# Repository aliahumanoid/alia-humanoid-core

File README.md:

<p align="center">
  <picture>
    <source media="(prefers-color-scheme: dark)" srcset="docs/media/alia-banner-dark.png">
    
  </picture>
</p>

# Alia Humanoid

**Building humanoid mechanics inside real human proportions.**

<table>
<tr>
<td width="70%">

</td>
<td width="30%">

</td>
</tr>
<tr>
<td align="center"><i>Lower leg assembly — human scale comparison</i></td>
<td align="center"><i>Right ankle prototype — 2-DOF motion test</i></td>
</tr>
</table>

<table>
<tr>
<td width="65%">
  
</td>
<td width="35%">
  
</td>
</tr>
<tr>
<td align="center"><i>Knee joint overlay — Joint Design Log #002</i></td>
<td align="center"><i>Right knee prototype — 1-DOF motion test</i></td>
</tr>
</table>

<table>
<tr>
<td align="center">

</td>
</tr>
<tr>
<td align="center"><i>First natural walking gait — physics simulation, motion-tracking RL (June 2026). Not hardware yet: sim-to-real is gated by remaining hardware.</i></td>
</tr>
</table>

---

## What We're Building

A humanoid robot designed from the ground up to fit within real human dimensions and proportions. 

Most humanoid projects scale UP for easier engineering — more space for motors, looser tolerances, simpler thermal management. We do the opposite: **building inside human constraints** forces design decisions — motor placement, transmission routing, thermal budget — that larger-envelope projects can avoid.

The result? A robot that can fit human environments, wear human clothing, and interact at human scale — using tendon-driven actuation, custom motor placement, and tight mechanical integration.

**Current Phase 0 Focus:** Lower body (hip + knee + ankle) — tendon-driven and direct-drive actuation.

### How We Develop in the Open

This repository carries the **replication core** — firmware, protocols, base host operation, hardware documentation, and results. Advanced lab tooling (calibration campaigns, learning-control experiments, gait tooling) is developed in a private suite and opens progressively as milestones mature. Results, videos, logs, and writeups continue to be published openly. We publish what fails alongside what works; simulation results are labeled as simulation results.

### Latest Updates
- 2026-11-09: Joint Design Log #003 (Hip) published — [YouTube](https://youtu.be/a9sh70xy4z0)
- 2026-09: **Hip roll motor integrated — first 3-DOF runs on the bench.** The two tendon-driven DOFs and the direct-drive roll now run together on one joint controller; results with the next Joint Design Log
- 2026-08-27: **Hip on the bench — first run at natural walking speed.** The 2-DOF tendon-driven hip tracks a gait-like reference (flexion and abduction sines in quadrature, 1.1 s cycle), free swing with no external load, with one learned feed-forward correction from a previous run (uncorrected at the same speed: 6.0° / 2.0° rms): 27 cycles, 2.95° / 1.37° rms, repeatable run to run — [X post](https://x.com/AliaHumanoid/status/2092992852150108425) (the post calls it the simulation policy's walking trajectory; the reference was a synthetic gait-like cycle)
- 2026-08: Direct-drive hip roll validated on a separate single-motor bench, free shaft (reference persistence, sweeps; a ±6° segment of the simulated walking trajectory tracked on hardware at 0.28° rms with the motor-internal loop, best run after timing and learning-control correction)
- 2026-07: **Development drop** — control-loop rate hardening (bench-validated to 625 Hz on the ankle), joint-map capture improvements, saved-offset warm-boot fast path, MOTION GUARD V2 (gait-aware safety guards; ships disabled, bench validation pending), host impedance-stream `tau_ff` channel — [details](PUBLIC_UPDATES.md)
- 2026-07-18: **Technical note published:** [Deterministic boot-time offset reconstruction for tendon-driven joints](https://aliahumanoid.com/notes/deterministic-boot-offset-reconstruction.html) — method published as prior art
- 2026-07: **License change:** software is GPLv3 from this release (prior MIT snapshots remain MIT); protocol specs stay MIT; hardware licensing unchanged — [rationale](PUBLIC_UPDATES.md)
- 2026-06-04: **First natural walking gait in simulation** — motion-tracking RL on the lower body, ONNX-verified locally — [X thread](https://x.com/AliaHumanoid/status/2062545958991265831) · [details](PUBLIC_UPDATES.md)
- 2026-06: Per-joint power board (`rev_d_power`) bench-validated end-to-end — closed-loop motor control on real hardware, 0.08° tracking error ([report](hardware/electronics/joint_controller_board/rev_d_power/BENCH_VALIDATION_REPORT.md) · [known issues](hardware/electronics/joint_controller_board/rev_d_power/README.md))
- 2026-04: Hip hybrid firmware path implemented (3 DOF / 5 motors)
- 2026-01-26: Joint Design Log #002 (Knee) published — [YouTube](https://youtu.be/4jU5Na2z-s8) · [X thread](https://x.com/AliaHumanoid/status/2015812906101657848)
- 2025-11-13: Joint Design Log #001 (Ankle) published — [YouTube](https://youtu.be/1Z9GlTnYEFs)
- 2025-10-31: Phase 0 public release — [PUBLIC_UPDATES.md](PUBLIC_UPDATES.md)

### Key Features

- 🦶 **2-DOF Ankle Joint**
  Plantarflexion/dorsiflexion (-50° to +25°) + inversion/eversion (±25°)

- 🦵 **1-DOF Knee Joint**
  Full flexion/extension (0° to 100°) with antagonistic tendon pair

- 🦴 **3-DOF Hip Joint (Hybrid)**
  Flexion/extension + abduction/adduction (tendon-driven) + axial roll (direct-drive), 5 motors

- 🧵 **Tendon-Driven Actuation**
  Antagonistic motor pairs with cascade PID, plus single direct-drive for hip roll

- 📏 **Human-Scaled Design**  
  Designed inside real human leg envelope — not scaled up

- ⚙️ **Real Hardware Iteration**  
  PA12 nylon structure (multi jet fusion), pin-and-bushing joints, UHMWPE tendons

- 🖥️ **Jetson Multi-Joint Controller**
  CAN-direct impedance streaming at 50Hz, automated exercise patterns, CAN-first diagnostics

- 🚶 **Walking — In Simulation**
  Natural full-amplitude gait via motion-tracking RL (knee ROM ~57°, foot clearance ~14 cm); sim-to-real gated by remaining hardware

- 📂 **Files released in phases**
  Phased licensing roadmap: STL → STEP → CAD source

---

## What Works ✅ / What Doesn't ⚠️

We document **both successes and failures** transparently.

> **Safety:** before powering any joint, read [Known safety limitations](SAFETY_LIMITATIONS.md).

**Current validation snapshot: knee and ankle closed as architecture baselines; per-joint power board bench-validated (known issues documented); hip tendon DOFs validated on the bench and the direct-drive roll on a single-motor bench, first 3-DOF runs on the bench; natural walking gait achieved in simulation, gait-like trajectory tracked on the physical hip at natural walking speed**

### ✅ Validated On Hardware (Phase 0)

- Knee validated as single-controller baseline (`L1` closed) — [Joint Design Log #002](https://youtu.be/4jU5Na2z-s8)
- Ankle validated as single-controller baseline (`L2` closed) — [Joint Design Log #001](https://youtu.be/1Z9GlTnYEFs)
- Multi-joint Jetson coordination operational on bench (`KNEE_RIGHT + ANKLE_RIGHT`) — [milestone log](PUBLIC_UPDATES.md)
- Protocol v1.0 freeze documented for the current knee+ankle bench baseline — [CAN system architecture §4.5](software/docs/CAN_SYSTEM_ARCHITECTURE.md)
- Ankle kinematics achieve target ROM (2 DOF within human envelope) — [joint specs](docs/specs/README.md)
- Knee ROM and tendon-driven position control validated (0-100 degrees)
- UHMWPE tendons validated for current bench loads and pulley compatibility — [tendon specs](docs/specs/TENDON_SPECIFICATIONS.md)
- PA12 structure passes current static/load validation
- Peak torque within biomechanics requirements at the validated bench conditions — [motor specs](docs/specs/MOTOR_SPECIFICATIONS.md)
- Rolling impedance control via CAN with cascade PID on the validated tendon-driven joints — [operational guide](software/docs/SET_IMPEDANCE_OPERATIONAL_GUIDE.md)
- Per-joint power board (`rev_d_power`) validated end-to-end: power rails, hot-swap protection, health telemetry, closed-loop motor control (0.08° tracking error) — [bench report](hardware/electronics/joint_controller_board/rev_d_power/BENCH_VALIDATION_REPORT.md) · [known issues](hardware/electronics/joint_controller_board/rev_d_power/README.md) (motor rail sags on touch or gate-node contamination; handling rules)

### 🧪 Validated In Simulation (Not Hardware)

- Natural full-amplitude walking gait via motion-tracking RL (knee ROM ~57°, foot clearance ~14 cm)
- Policy exported to ONNX and verified locally with observation-parity checks
- Robustness via domain randomization (actuator gains, latency, mass) grounded in measured bench data
- **Honest boundary:** simulation results are simulation results — hardware walking requires foot sole, batteries and full-leg integration first

### ✅ Hip — Per-Axis Bench Validation (August–September 2026)

Bench runs used firmware changes that ship with the next release, and host-side gait-replay tooling (timing and learned corrections) that stays in the private suite; this release carries the hybrid model and the `HIP_ROLL_BENCH_*` profiles.

- Hip hybrid model (`3 DOF / 5 motors`, per-DOF `DriveType` / `DofCapabilityFlags`) exercised on hardware: both tendon-driven DOFs mapped, calibrated and driven with the hybrid-aware auto-mapping path (known issue: at the end of a mapping run all motors are released and, with the tendons slack, a gravity-loaded limb drops freely; support the limb before the run ends; a slow slack take-up is in development)
- Joint encoders zeroed at the CAD mechanical stops, persistent across power cycles
- Gait-like reference (flexion and abduction sines in quadrature, 1.1 s cycle) tracked on the physical hip (2 tendon-driven DOFs) at natural walking speed, free swing with no external load, with one learned feed-forward correction from a previous run (uncorrected at the same speed: 6.0° / 2.0° rms): 27 cycles, 2.95° / 1.37° rms, repeatable run to run — [X post](https://x.com/AliaHumanoid/status/2092992852150108425) (the post calls it the simulation policy's walking trajectory; the reference was a synthetic gait-like cycle)
- Direct-drive axial roll validated on a separate single-motor bench, free shaft (`HIP_ROLL_BENCH_*` profiles): reference persistence across power cycles, sweeps, a ±6° segment of the simulated walking trajectory tracked on hardware at 0.28° rms with the motor-internal loop (best run, after timing and learning-control correction)

### 🛠️ Implemented In Firmware, Pending Bench Validation

- MOTION GUARD V2 — gait-aware divergence/stall guards behind a runtime mode switch (ships in LEGACY mode = current behavior; SHADOW/ACTIVE pending bench validation)

### ⚠️ Still Iterating

- Hip: roll motor mounted, the two tendon-driven DOFs and the roll run together on one controller (September 2026); 3-DOF tracking on the bench in progress, results with the next Joint Design Log, then mounting into the full right leg
- Full hip 3-DOF integrated validation (L3)
- Multi-controller integrated test (L5: hip + knee + ankle on Jetson)
- Walking gait as integrated lower-body system **on hardware**
- Sim-to-real transfer (policy deployment on the onboard computer; gated by foot sole, power boards at scale, batteries)
- Power board high-current stress testing (22A continuous / ~38A peak)

---

## Architecture

```
Jetson host (Python)          RP2350 joint controller (C++)          Motors
SET_IMPEDANCE @50Hz  --CAN-->  core0: encoders (MT6835, SPI)   --CAN--> antagonistic
per-DOF gains/tau_ff           core1: cascade PID + safety              tendon pairs
                               (bench-validated to 625 Hz)              (+ direct-drive hip roll)
```

- [CAN system architecture](software/docs/CAN_SYSTEM_ARCHITECTURE.md) — protocol, IDs, freeze policy
- [SET_IMPEDANCE operational guide](software/docs/SET_IMPEDANCE_OPERATIONAL_GUIDE.md) — the impedance streaming interface
- [Firmware update protocol spec](software/docs/CAN_FIRMWARE_UPDATE_PROTOCOL_SPEC.md) — CAN-based firmware updates

## Build & Run

**Host (runs without hardware):**
```bash
cd software/host && python3 -m venv venv && . venv/bin/activate
pip install -r requirements.txt && python main.py   # web UI on :5001
```

**Firmware (PlatformIO, RP2350 Pico 2):**
```bash
cd software/firmware/joint_controller && pio run
```

Bench bring-up: [Jetson single-controller checklist](software/docs/JETSON_SINGLE_CONTROLLER_BRINGUP_CHECKLIST.md). Minimum bench: one joint controller board, CAN adapter, 24V supply.

## Current Status (Phase 0)

Last reviewed: 2026-11-09. Ankle and knee validated as single-controller baselines; hip on the bench; walking shown in simulation only.

| Component | Status | License | Notes |
|-----------|--------|---------|-------|
| **Software** | ✅ Public | GPLv3 | Python host + C++ firmware (RP2350 Pico 2); releases before July 2026 remain MIT |
| **Hardware Docs** | ✅ Public | CC BY-NC-ND | Assembly guides, BOM, design specs |
| **STL Files** | ✅ Public | CC BY-NC-ND | 19 files: ankle, lower leg, common components |
| **Electronics** | ✅ Public | CC BY-NC-ND | RP2350 controller board + per-joint power board (KiCad source, Gerber, STEP) |
| **CAD Source** | 📅 Phase 2+ (TBD) | CC BY-SA | Full parametric Fusion 360 timeline |

See our [licensing roadmap](hardware/LICENSE.md) for details on what is released when.

---

## Quick Links

- 📺 **[YouTube Channel](https://www.youtube.com/@aliahumanoid)** — Design logs, demos, technical breakdowns
- 🐦 **[X/Twitter (@AliaHumanoid)](https://x.com/AliaHumanoid)** — Project updates, iteration logs
- 🌐 **[Website](https://aliahumanoid.com)** — Project overview and roadmap
- 📝 **[Public Updates](PUBLIC_UPDATES.md)** — Public milestone log and release notes
- 📖 **[Documentation](software/README.md)** — Software architecture, protocols, build guides
- 📐 **[Technical Specs](docs/specs/README.md)** — Joint specifications, motor specs, tendon specs
- 🗒️ **[Technical Notes](https://aliahumanoid.com/notes/deterministic-boot-offset-reconstruction.html)** — Method writeups published as prior art

**Evaluating this project? Start here:** (1) watch a [joint design log](https://youtu.be/1Z9GlTnYEFs), (2) read the [boot-reconstruction technical note](https://aliahumanoid.com/notes/deterministic-boot-offset-reconstruction.html), (3) read the firmware control loop (`software/firmware/joint_controller/src/JointController_ControlLoop.cpp`). Issues with findings are welcome.

---

## Gallery

<table>
<tr>
<td width="50%">

<p align="center"><i>Physical prototype assembly (Phase 0)</i></p>
</td>
<td width="50%">

<p align="center"><i>Ankle cutaway showing tendon routing</i></p>
</td>
</tr>
</table>

---

## Project Roadmap

### Phase 0 (Current) — Prove the Concept
- **Focus:** Lower body (hip + knee + ankle) validation
- **Release:** Software (GPLv3 from the July 2026 release; earlier snapshots remain MIT), Hardware docs + STL (CC BY-NC-ND)
- **Timeline:** In progress

### Phase 1 — Expand Hardware
- **Focus:** Full leg (hip, knee, ankle), upper body planning
- **Release:** STL → STEP files (CC BY-NC-SA)
- **Timeline:** Planned

### Phase 2 — Full Collaboration
- **Focus:** Complete humanoid system integration
- **Release:** CAD source files (CC BY-SA), governance formalized
- **Timeline:** TBD

### Phase 3 — Open-Core Model
- **Focus:** The software open-core boundary is active now (formalized early, July 2026): this repo = replication core; advanced lab tooling opens progressively as milestones mature
- **Release:** Hardware follows the phased CC roadmap above; private components promote to public at milestone gates
- **Timeline:** Boundary active; promotions ongoing

---

## Follow Progress

This repository documents Phase 0 validation work in public. Small software/docs improvements and evidence-based feedback are welcome. See [CONTRIBUTING.md](CONTRIBUTING.md) for the current collaboration boundary.

**Ground Rules:**
- All commits require DCO sign-off: `git commit -s`
- Use English for code/comments/issues
- Follow conventional commit format (`feat:`, `fix:`, `docs:`, etc.)

**Current Accepted PR Scope:**
- 🐛 Bug reports and fixes
- 📖 Documentation improvements (clarity, examples, translations)
- 🧪 Testing and validation reports (especially hardware replication)
- 💡 Feature proposals (via issues first)

**Not Yet Open As PR Surface:**
- Hardware geometry changes to STL/CAD assets
- Canonical hardware design modifications while the public hardware release remains STL-only

For hardware design ideas, replication findings, and geometry feedback, open an issue first with evidence, measurements, or photos.

---

## References & Acknowledgments

### Control Architecture

The cascade control structure implemented for antagonistic tendon-driven actuation is inspired by the approach described in:

> **Lukić B., Jovanović K., Šekara T. B. (2019).**  
> *Cascade Control of Antagonistic VSA — An Engineering Control Approach to a Bioinspired Robot Actuator.*  
> Frontiers in Neurorobotics, Vol. 13, Article 69.  
> DOI: [10.3389/fnbot.2019.00069](https://doi.org/10.3389/fnbot.2019.00069)

The original paper presents a double-loop cascade architecture for simultaneous position and stiffness control of an antagonistic Variable Stiffness Actuator (VSA). 

In Alia's implementation, this concept has been extended and generalized to a multi-DOF humanoid control system, featuring:
- Coordinated cascade loops for multiple joints
- Per-DOF tuning of PID gains (inner loop: motor position, outer loop: joint position)
- Dynamic modulation of cascade influence and stiffness reference
- Synchronized trajectory generation for agonist–antagonist motor pairs

This implementation is an independent engineering development released under the GNU GPLv3 (releases before July 2026: MIT).

---

## License

- **Software (firmware + host):** [GNU GPLv3](LICENSE) from the July 2026 release onward. Releases published before July 2026 were MIT and remain MIT — irrevocable for anyone who obtained them.
- **Protocol specifications** ([CAN system architecture](software/docs/CAN_SYSTEM_ARCHITECTURE.md), [firmware-update protocol](software/docs/CAN_FIRMWARE_UPDATE_PROTOCOL_SPEC.md)): **MIT**, so third-party tools can integrate without copyleft obligations.
- **Hardware:** unchanged — see [hardware/LICENSE.md](hardware/LICENSE.md) for the phased CC roadmap.

By contributing code, you license it under GPLv3 (DCO sign-off required). Hardware design feedback is welcome now; canonical hardware geometry changes will open later as the hardware release surface expands.

---

### How the pieces fit (what protects what)

| Layer | License / instrument | What it means in practice |
|---|---|---|
| Firmware + host software | **GPLv3** (July 2026 onward; earlier snapshots remain MIT) | Commercial use is allowed; modified versions must stay GPLv3; no locked-down derivatives |
| Protocol specifications | **MIT** | Third-party tools can implement the protocols without copyleft obligations |
| Hardware (STL, docs, BOM) | **CC BY-NC-ND 4.0** today → CC BY-NC-SA (STEP) → CC BY-SA (CAD source) | Print and study now; no commercial use or derivatives yet; opens in phases, see [hardware/LICENSE.md](hardware/LICENSE.md) |
| Published technical notes | **Public prior art** | Keeps the methods free for everyone to use: nobody can patent them later. Prior art does not restrict copying; the licenses above do |
| Name and logo | Not covered by any of the above | Trade mark rules apply separately |

ALIA HUMANOID is a registered EU trade mark (EUTM 019380142). The name and the brand are not covered by the open licenses of this repository.

## Developer Certificate of Origin (DCO)

All commits must include a `Signed-off-by` line to certify you have the right to contribute:

```bash
git commit -s -m "feat: add ankle calibration script"
```

This asserts compliance with the [Developer Certificate of Origin](https://developercertificate.org/).

---

## Contact

- **General:** info@aliahumanoid.com
- **Issues/PRs:** Use GitHub issues and pull requests
- **Social:** [@AliaHumanoid](https://x.com/AliaHumanoid) on X/Twitter

---

**Project Status:** Phase 0 active development

---

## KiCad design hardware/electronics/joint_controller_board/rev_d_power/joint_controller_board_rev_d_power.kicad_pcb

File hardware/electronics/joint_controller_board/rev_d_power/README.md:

# rev_d_power

Power board for split Rev D architecture (`40 mm x 60 mm`).

Reference documents:
- `../docs/rev_d_architecture.md`
- `ARCHITECTURE.md`
- `COMPONENT_SELECTION.md`
- `rev_d_power_parts.kicad_sym`

Status:
- KiCad project files refreshed from `rev_d_logic` on `2026-04-13`
- redesign target remains `24V` input domain
- `.kicad_pro`, rules, symbol table, and supporting project files are aligned to the `rev_d_logic` template
- `ARCHITECTURE.md` is the authoritative design direction for the new power board
- current schematic draft now includes:
  - `RJ45` interface connector with frozen split-architecture pinout
  - `XT60` raw input: `J2`, XT60PW-F female
  - `XT60` switched output: `J4`, XT60PW-M male
  - no raw daisy-chain connector; upstream fan-out is handled by the PDU
  - input protection network with `SMCJ33A`, raw bulk capacitor, raw decoupling capacitor
  - high-side `TPS2492` hot-swap / eFuse controller driven by `SAFETY_EN`, with
    `Ilim ≈ 33.3 A` on the PCBWay first lot (`R4 = WSR31L500FEA`, 1.5 mΩ)
    and latch-off on fault (branch fuse intentionally moved off-board to
    upstream PDU — see `ARCHITECTURE.md` "External fusing")
  - `LMR36520`-based `24V -> 5V` buck draft for `+5V_FROM_POWER`
  - `TLV75533P`-based `5V -> 3V3` auxiliary LDO draft for monitor/status conditioning
  - `PWR_FLAG` markers on `24V_RAW`, `+5V_FROM_POWER`, and `GND` for clean ERC intent
  - official KiCad library symbols already adopted for:
    - `LMR36520ADDA` for the `LMR36520ADDAR` buck
    - `TLV70012_SOT23-5` as schematic base symbol for `TLV75533PDBV`
    - `Device:L` for the buck output inductor
  - first-pass analog monitors:
    - `VIN_RAW_MON` divider + RC
    - `VOUT_POST_FET_MON` divider + RC
  - first-pass status conditioning:
    - `PWRGD_N` 3.3 V pull-up
    - `FAULT_N` 3.3 V pull-up
- schematic ERC is currently at `0` errors / `0` warnings
- PCB DRC is currently at `0` violations after zone refill
- primary semiconductor selection is now frozen at architecture level:
  - high-side controller / eFuse
  - `24V -> 5V` regulator
  - `5V -> 3V3` regulator
  - input TVS
- electrical design envelope is now frozen in `ARCHITECTURE.md` for first-pass sizing:
  - worst-case local branch = HIP profile with `5` motors
  - motor sizing baseline = `24V`, `4.4 A` continuous each, `7 Nm` peak, `10:1`
  - switched branch target = `22 A` continuous, `40 A` class transient tolerance
  - logic-board rail target = `+5V_FROM_POWER @ 1 A continuous`
- first-pass primary semiconductors are now selected in `COMPONENT_SELECTION.md`:
  - `TPS2492` hot-swap / eFuse controller
  - back-to-back `BSC016N06NS` switched-path MOSFET pair
  - `LMR36520` main `24V -> 5V` buck
  - `TLV75533P` auxiliary `5V -> 3V3` LDO
  - `SMCJ33A` input TVS
- validation feedback has been folded into the design notes:
  - `TPS2492` is treated as a fixed-`50 mV` current-limit device
  - PCBWay first-lot shunt = `1.5 mOhm`, Kelvin sensed, `3W` (`WSR31L500FEA`)
  - `IMON` is intentionally not routed to RJ45 in this revision because the connector pin budget is full
  - MOSFET thermal layout must assume the `22 A` HIP envelope from day one
- local symbol library now exists for the selected active devices:
  - `rev_d_power_parts.kicad_sym`
  - project `sym-lib-table` updated to reference it
- local footprint library now freezes board-approved mechanical footprints:
  - `rev_d_power_footprints.pretty/AMASS_XT60PW-F_1x02_P7.20mm_Horizontal.kicad_mod`
  - `rev_d_power_footprints.pretty/AMASS_XT60PW-M_1x02_P7.20mm_Horizontal.kicad_mod`
  - the XT60 peg slots intentionally match the already-produced `motor_can_power_hub_rev_a` geometry (`0.6 mm x 1.7 mm` oval slot, local rotation `270`)

Bench validation:
- the PCBWay first article is bench-validated end-to-end (`2026-06`) — see `BENCH_VALIDATION_REPORT.md` for full detail
- coverage: bare-board continuity, rails, `TPS2492` hot-swap + back-to-back FET path, telemetry, `FAULT_N` handling, and closed-loop control of a real motor with safety-limit enforcement; all bring-up phases graded `PASS`
- headline numbers:
  - rails at `24V`: buck `+5V_FROM_POWER` = `5.0 V`, `3V3_AUX` LDO OK
  - `VIN_RAW_MON` = `2.18 V` exact (`24V x 8.2/90.2`), confirming divider precision
  - `TPS2492` soft-start brings `J4` to `24V` in `<` a few ms; `PWRGD_N` confirmed `ACTIVE-LOW`, `R1 = 100k` `SAFETY_EN` pulldown gives deterministic OFF default
  - closed-loop motor (joint `8`, `hip_roll_bench_right`, direct-drive): `0.08 deg` steady-state tracking error, control loop `~350 us` avg (budget `2000 us`), `0` CAN errors
  - safety layer clamps a `+40 deg` command into the conservative `[-38.5, +38.5] deg` range (`1.5 deg` inside the hard `±40 deg` limit) gracefully (WARN + clamp, no fault/E-stop)
- `PWRGD_N` / `FAULT_N` active-low polarity assumptions (written before hardware) are now confirmed on real hardware — no firmware polarity changes needed
- still pending (not done): Phase 7 high-current stress (`22 A` continuous / `~38 A` peak) and `TPS2492` real-hardware overcurrent latch-off, both needing a battery / stiff supply + external `30 A` ATO fuse + real load
- the validated first lot uses `R4 = WSR31L500FEA` (`1.5 mOhm` `3W` Kelvin shunt, `TPS2492 Ilim ≈ 33.3 A`, PCBWay-approved first-lot substitution — consistent with the body above) and `D2 = SS56B-HF`; see `BENCH_VALIDATION_REPORT.md`

Known issues (found after the June bench validation):
- **The motor rail sags or switches off when the board is touched while powered** (found 2026-08-01, reproducible). The `TPS2492` drives the pass-FET gate from a current source of a few tens of µA. Leakage of the same order into the gate node partially discharges it: the FET moves into its linear region and the switched motor rail (`J4`) sags, or turns off completely, while `VIN` stays steady and `PWRGD_N` stays asserted — so the board's own status does not flag it, and the motors lose supply mid-motion. A bare finger on the board is enough; flux residue, dust with humidity or condensation can leak the same current with nobody touching the board. Gloved or tool contact had no effect: this is a property of the µA-level gate drive, not an assembly defect.
  - never touch the power board while it is powered;
  - clean the gate area with isopropyl alcohol after soldering and keep the board dry; a conformal coating is being evaluated;
  - firmware: a motor-rail supervisor (reads `VOUT_POST_FET_MON`, declares the rail lost and stops the joint) ships with the next release.
- **The upstream `30 A` ATO branch fuse cannot clear against a current-limited 24 V converter.** A blade fuse needs several times its rating to open within seconds; typical 24 V converters limit their current (foldback, hiccup or latching shutdown) well below that. With such a source, a short on one branch collapses the whole 24 V rail instead of opening that branch's fuse. Per-branch protection is therefore electronic — the `TPS2492` current limit on each board (`~33.3 A` with the first-lot shunt); the fuse protects the wiring only when the source can deliver the fault current (e.g. a battery).

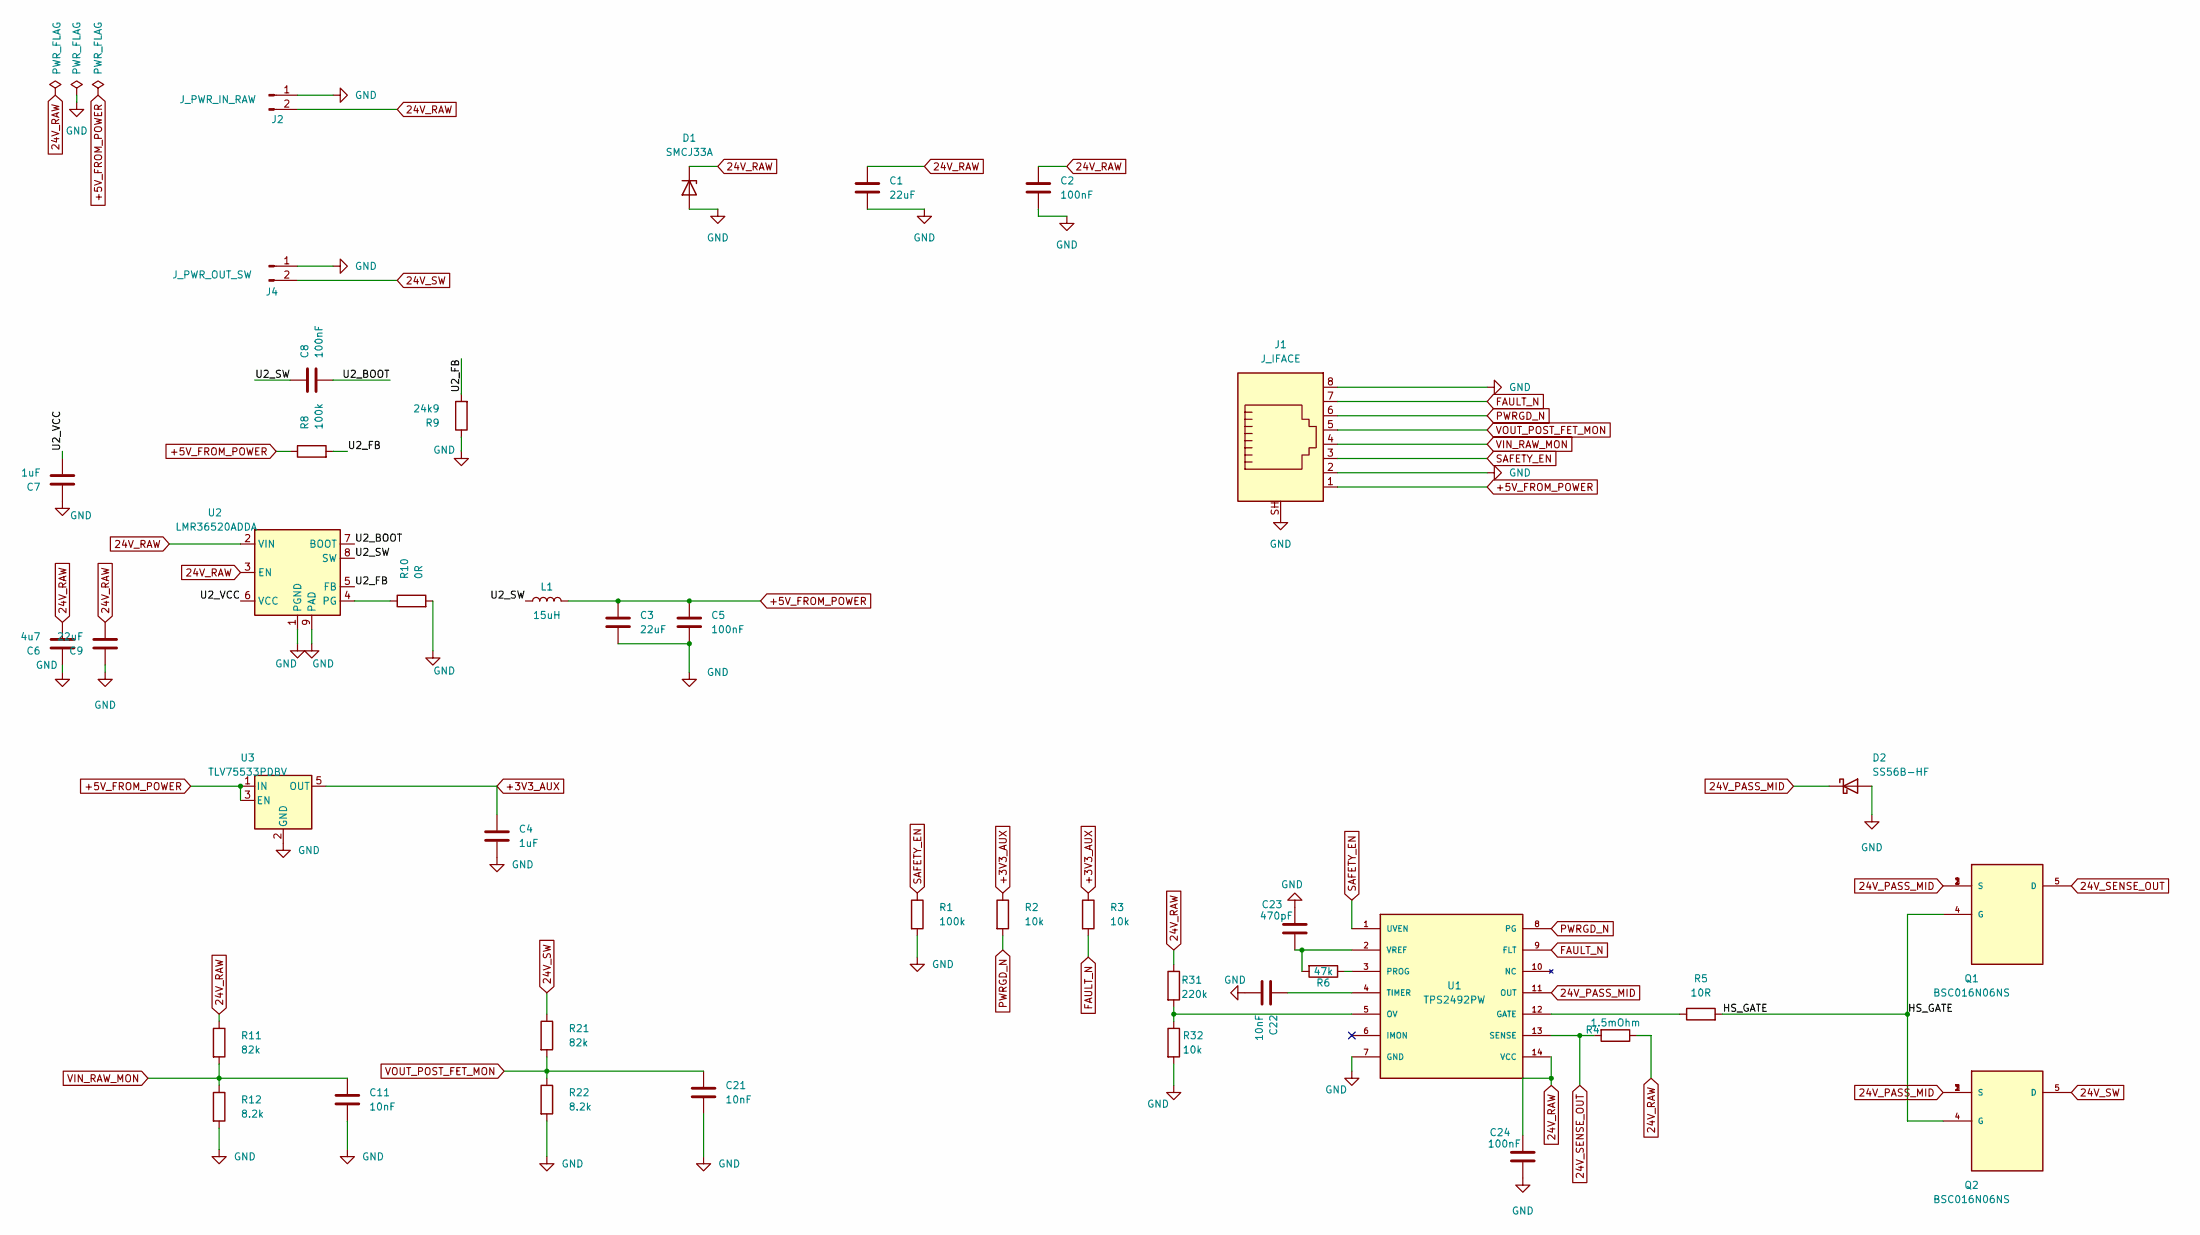
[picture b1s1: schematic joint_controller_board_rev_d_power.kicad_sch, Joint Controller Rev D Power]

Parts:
C1, C9: 22uF; C_1210_3225Metric
C2, C5, C8, C24: 100nF; C_0805_2012Metric
C3: 22uF; C_0805_2012Metric
C4, C7: 1uF; C_0805_2012Metric
C6: 4u7; C_1210_3225Metric
C11, C21, C22: 10nF; C_0805_2012Metric
C23: 470pF; C_0805_2012Metric
D1: SMCJ33A; D_SMC; MPN SMCJ33A
D2: SS56B-HF; D_SMB; MPN SS56B-HF
J1: J_IFACE; RJ45_Amphenol_RJHSE5380; MPN RJHSE-5380
J2: J_PWR_IN_RAW; AMASS_XT60PW-F_1x02_P7.20mm_Horizontal; MPN XT60PW-F
J4: J_PWR_OUT_SW; AMASS_XT60PW-M_1x02_P7.20mm_Horizontal; MPN XT60PW-M
L1: 15uH; L_Bourns_SRP5030T; MPN SRP5030T-150M
Q1, Q2: BSC016N06NS; TDSON-8-1; MPN BSC016N06NSATMA1
R1, R8: 100k; R_0805_2012Metric
R2, R3, R32: 10k; R_0805_2012Metric
R4: 1.5mOhm; R_Shunt_Vishay_WSR2_WSR3_KelvinConnection; MPN WSR31L500FEA
R5: 10R; R_0805_2012Metric
R6: 47k; R_0805_2012Metric
R9: 24k9; R_0805_2012Metric
R10: 0R; R_0805_2012Metric
R11, R21: 82k; R_0805_2012Metric
R12, R22: 8.2k; R_0805_2012Metric
R31: 220k; R_0805_2012Metric
U1: TPS2492PW; TSSOP-14_4.4x5mm_P0.65mm; MPN TPS2492PW
U2: LMR36520ADDA; Texas_HTSOP-8-1EP_3.9x4.9mm_P1.27mm_EP2.95x4.9mm_Mask2.4x3.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; MPN LMR36520ADDAR
U3: TLV75533PDBV; SOT-23-5; MPN TLV75533PDBVR

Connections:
24V_PASS_MID: D2.1 (K), Q1.1 (S), Q1.2 (S), Q1.3 (S), Q2.1 (S), Q2.2 (S), Q2.3 (S), U1.11 (OUT)
24V_RAW: C1.1, C2.1, C6.2, C9.2, C24.2, D1.1 (K), J2.2, R4.1, R11.1, R31.1, U1.14 (VCC), U2.2 (VIN), U2.3 (EN)
24V_SENSE_OUT: Q1.5 (D), R4.2, U1.13 (SENSE)
24V_SW: J4.2, Q2.5 (D), R21.1
+3V3_AUX: C4.1, R2.1, R3.1, U3.5 (OUT)
+5V_FROM_POWER: C3.1, C5.1, J1.1, L1.2, R8.1, U3.1 (IN), U3.3 (EN)
/HS_GATE: Q1.4 (G), Q2.4 (G), R5.2
/U2_BOOT: C8.2, U2.7 (BOOT)
/U2_FB: R8.2, R9.2, U2.5 (FB)
/U2_SW: C8.1, L1.1, U2.8 (SW)
/U2_VCC: C7.2, U2.6 (VCC)
FAULT_N: J1.7, R3.2, U1.9 (FLT)
GND: C1.2, C2.2, C3.2, C4.2, C5.2, C6.1, C7.1, C9.1, C11.2, C21.2, C22.2, C23.2, C24.1, D1.2 (A), D2.2 (A), J1.2, J1.8, J1.SH, J2.1, J4.1, R1.2, R9.1, R10.2, R12.2, R22.2, R32.2, U1.7 (GND), U2.1 (PGND), U2.9 (PAD), U3.2 (GND)
unnamed: R5.1, U1.12 (GATE)
unnamed: R31.2, R32.1, U1.5 (OV)
unnamed: R6.1, U1.3 (PROG)
unnamed: C22.1, U1.4 (TIMER)
unnamed: C23.1, R6.2, U1.2 (VREF)
unnamed: R10.1, U2.4 (PG)
PWRGD_N: J1.6, R2.2, U1.8 (PG)
SAFETY_EN: J1.3, R1.1, U1.1 (UVEN)
VIN_RAW_MON: C11.1, J1.4, R11.2, R12.1
VOUT_POST_FET_MON: C21.1, J1.5, R21.2, R22.1

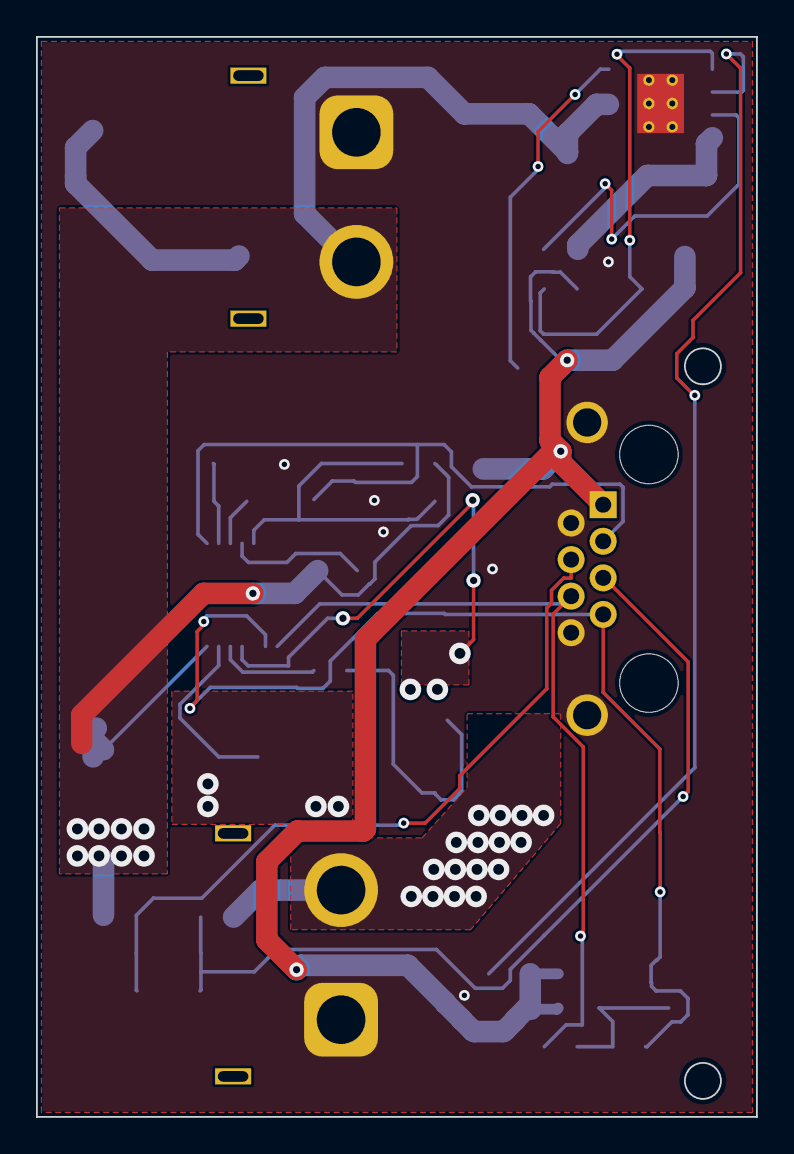
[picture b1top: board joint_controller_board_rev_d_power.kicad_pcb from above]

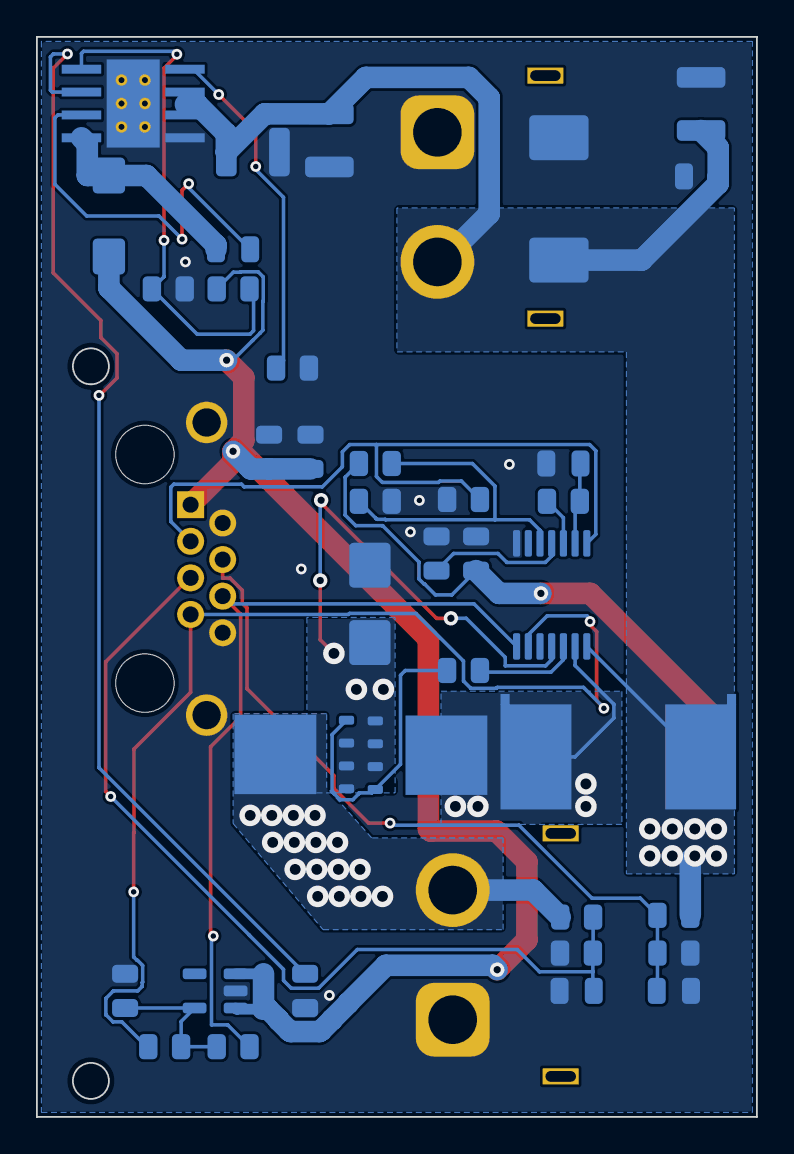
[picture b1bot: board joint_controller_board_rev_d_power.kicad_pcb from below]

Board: 2 copper layers, 40.0 x 60.0 mm, 40 parts (37 on the bottom side), 23 nets.

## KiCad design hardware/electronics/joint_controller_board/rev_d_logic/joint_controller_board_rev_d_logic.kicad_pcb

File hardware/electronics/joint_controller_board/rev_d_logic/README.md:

# Joint Controller Board Rev D Logic

**Status:** Current public controller board release  
**Board size:** 60 mm x 40 mm  
**Tool baseline:** KiCad 9.0.7

## Scope

`rev_d_logic` is the controller logic board currently exposed in the public repository. It is the RP2350-based control board that interfaces with motors, CAN, safety signals, and the external encoder hub.

## Main Features

- RP2350 Pico 2 host module
- Two onboard CAN channels (`CAN1`, `CAN2`) implemented with `MCP2515 + SN65HVD230`
- RJ45 interface connector for power/safety breakout
- RJ45 encoder connector compatible with `MT6835_hub_rev_a`
- KiCad source, BOM, board setup rules, and current PCB fabrication package

## Electrical Status

Latest validation used KiCad CLI checks on the current schematic/PCB pair.

- PCB DRC: 0 violations
- PCB unconnected pads: 0
- Schematic ERC: 0 errors, 0 warnings
- Final fabrication package includes the watchdog pad-spacing fix for `MAX6369`

## Connector Summary

### J1 - Interface RJ45

1. `+5V_FROM_POWER`
2. `GND`
3. `SAFETY_EN`
4. `VIN_RAW_MON`
5. `VOUT_POST_FET_MON`
6. `PWRGD_N`
7. `FAULT_N`
8. `GND`
Shield. `GND`

### J2 - Encoder RJ45

1. `GND`
2. `ENC_SCK`
3. `ENC_MOSI`
4. `ENC_MISO`
5. `CS_ENC1`
6. `CS_ENC2`
7. `CS_ENC3`
8. `+5V`
Shield. `GND`

### CAN terminal blocks

- `CAN1`: `GND`, `CAN1_L`, `CAN1_H`
- `CAN2`: `GND`, `CAN2_L`, `CAN2_H`

## Firmware GPIO Mapping

Shared SPI:

- `GP10` -> `SCK`
- `GP11` -> `MOSI`
- `GP12` -> `MISO`

CAN:

- `GP9` -> `CAN1_CS`
- `GP13` -> `CAN1_INT`
- `GP8` -> `CAN2_CS`
- `GP14` -> `CAN2_INT`
- `GP7` -> `CAN_RST_N`

Safety / watchdog:

- `GP15` -> `WDI`
- `GP22` -> `SAFETY_EN`

Encoder:

- `GP16..GP21` -> encoder SPI lines and `CS_ENC*`

Analog monitor inputs:

- `GP26_ADC0` -> `VIN_RAW_MON`
- `GP27_ADC1` -> `VOUT_POST_FET_MON`

Digital status inputs:

- `GP5` -> `PWRGD_N`
- `GP6` -> `FAULT_N`

## Included Files

- `joint_controller_board_rev_d_logic.kicad_sch`
- `joint_controller_board_rev_d_logic.kicad_pcb`
- `joint_controller_board_rev_d_logic.kicad_pro`
- `joint_controller_board_rev_d_logic.kicad_dru`
- `joint_controller_board_rev_d_logic.step`
- `BOM_fabrication_combined.csv`
- `UCC27282D.kicad_sym`
- `sym-lib-table`
- `check_footprints.sh`
- `fabrication_release_2026-02-22_wdt_padfix/rev_d_logic_fabrication_release_2026-02-22_wdt_padfix.zip`

## Notes

- The recommended fabrication package is the `wdt_padfix` release.
- Most 3D models referenced by the PCB come from the standard KiCad 9 model libraries.

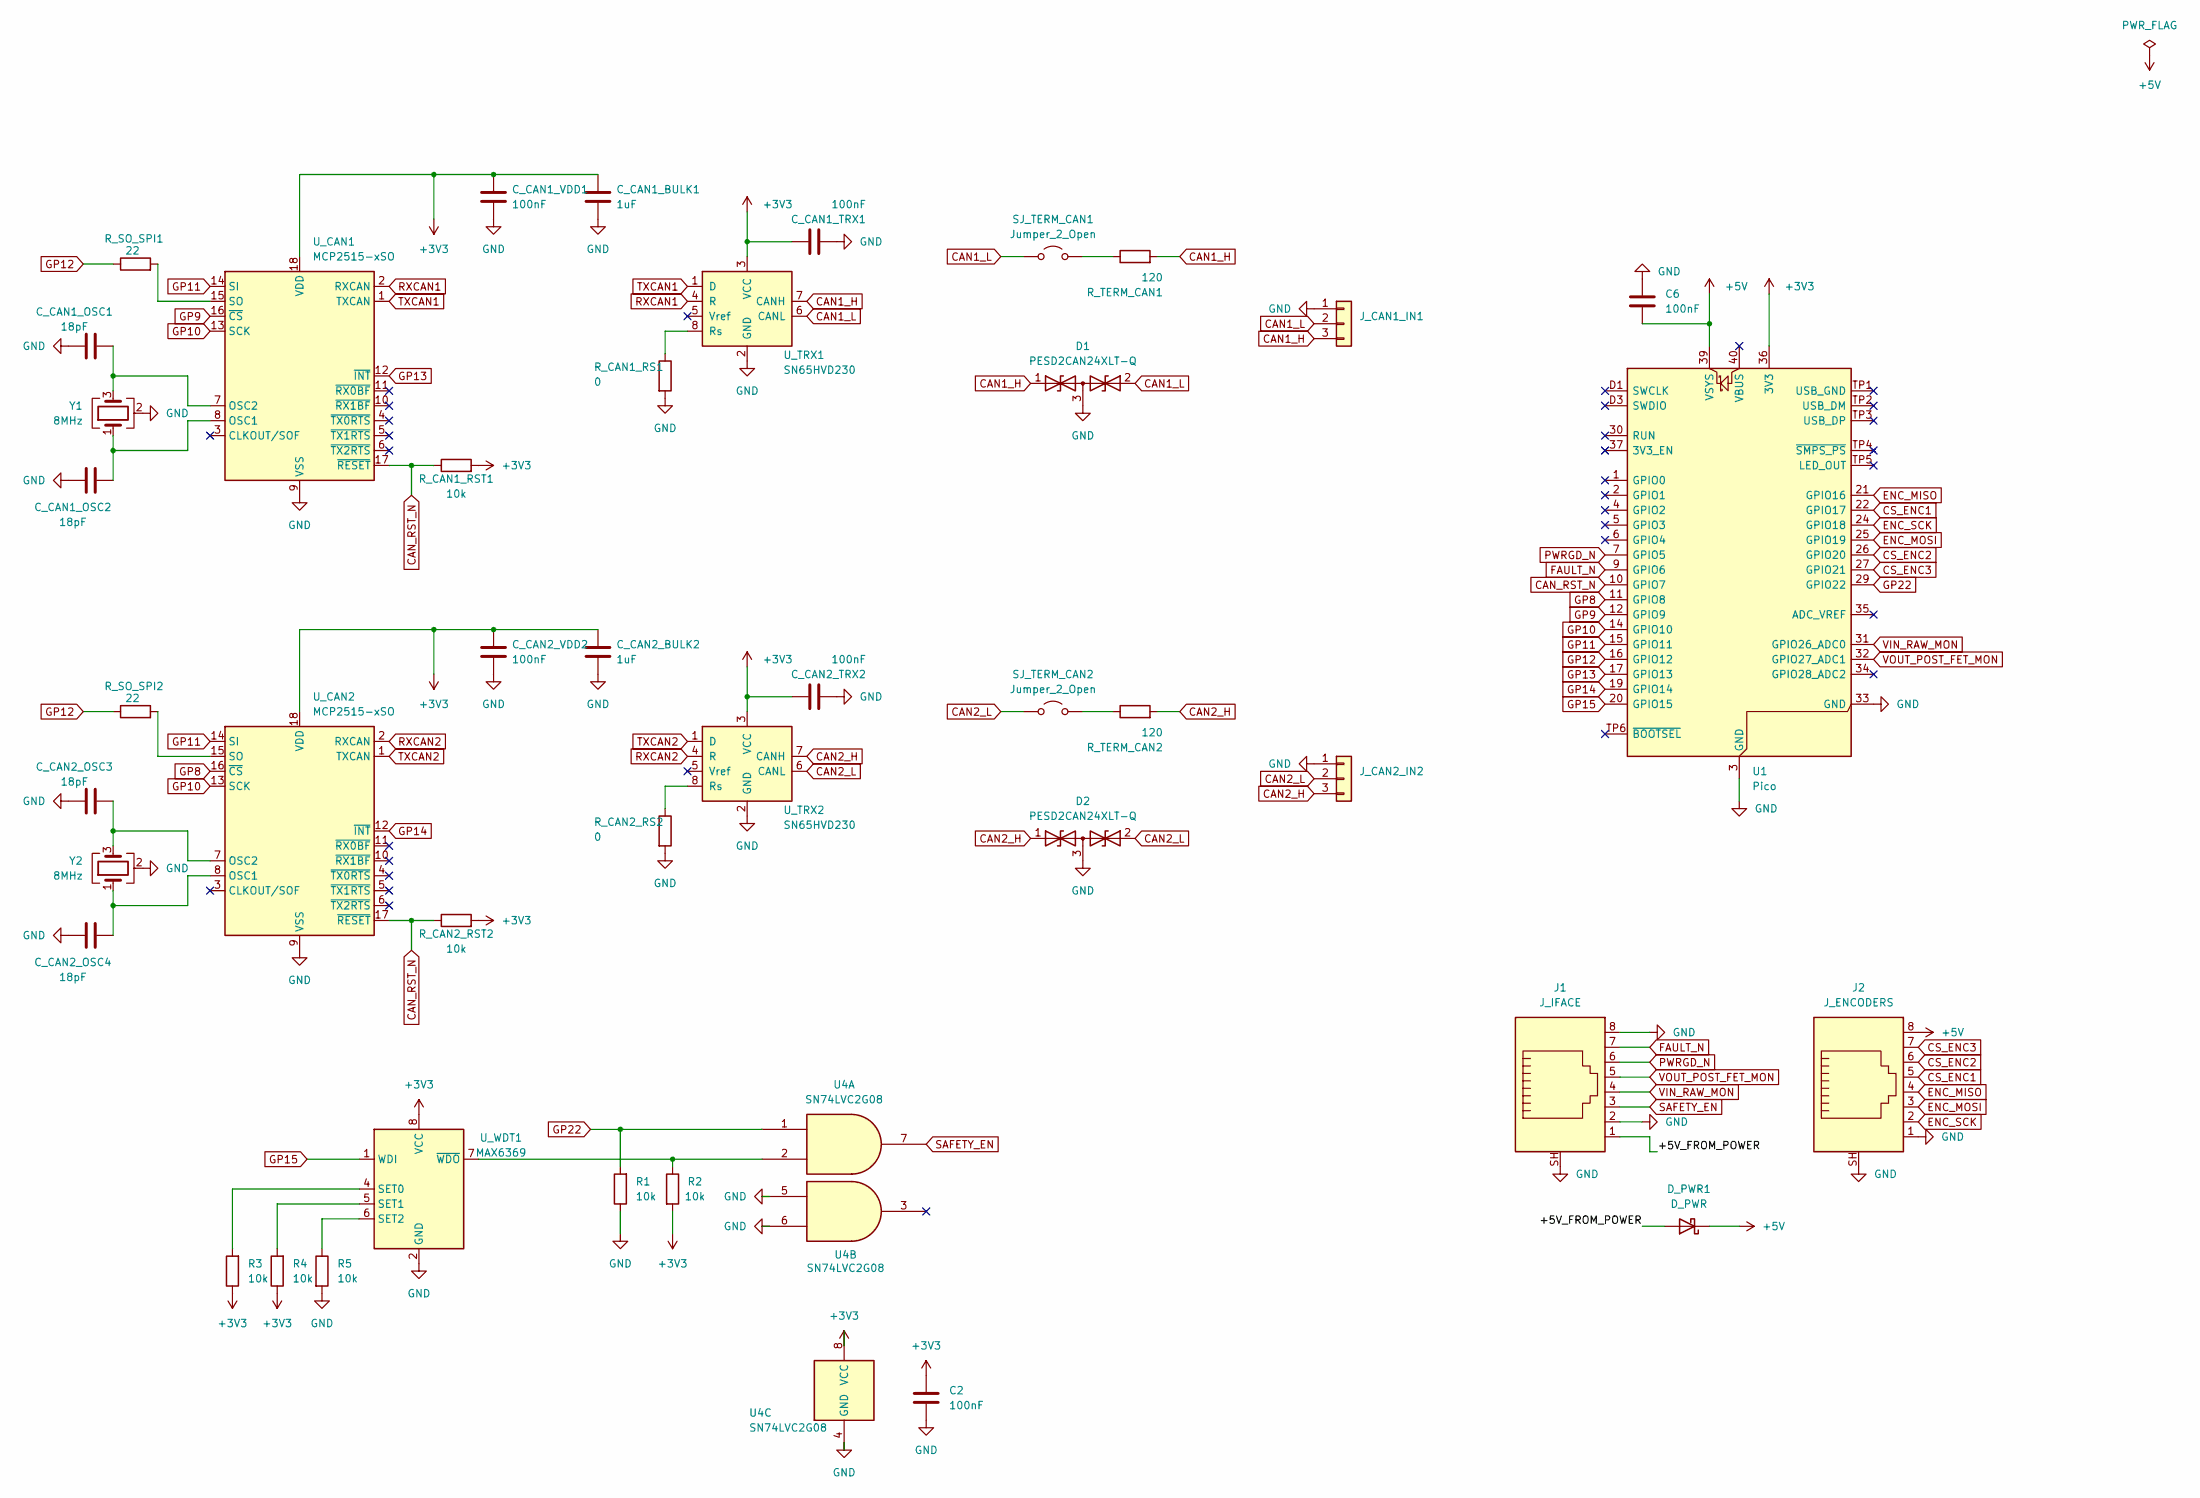
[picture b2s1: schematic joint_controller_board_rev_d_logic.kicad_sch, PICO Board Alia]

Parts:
C2, C6: 100nF; C_0805_2012Metric
C_CAN1_BULK1, C_CAN2_BULK2: 1uF; C_0805_2012Metric
C_CAN1_OSC1, C_CAN1_OSC2, C_CAN2_OSC3, C_CAN2_OSC4: 18pF; C_0805_2012Metric
C_CAN1_TRX1, C_CAN1_VDD1, C_CAN2_TRX2, C_CAN2_VDD2: 100nF; C_0805_2012Metric
D1, D2: PESD2CAN24XLT-Q; SOT-23
D_PWR1: D_PWR; D_SMA
J1: J_IFACE; RJ45_Amphenol_RJHSE5380
J2: J_ENCODERS; RJ45_Amphenol_RJHSE5380
J_CAN1_IN1, J_CAN2_IN2: TerminalBlock_Phoenix_MPT-0,5-3-2.54_1x03_P2.54mm_Horizontal
R1, R2, R3, R4, R5: 10k; R_0805_2012Metric
R_CAN1_RS1, R_CAN2_RS2: 0; R_0805_2012Metric
R_CAN1_RST1, R_CAN2_RST2: 10k; R_0805_2012Metric
R_SO_SPI1, R_SO_SPI2: 22; R_0805_2012Metric
R_TERM_CAN1, R_TERM_CAN2: 120; R_0805_2012Metric
SJ_TERM_CAN1, SJ_TERM_CAN2: Jumper_2_Open; SolderJumper-2_P1.3mm_Open_TrianglePad1.0x1.5mm
U1: Pico; RaspberryPi_Pico_Common_THT
U4: SN74LVC2G08; VSSOP-8_2.4x2.1mm_P0.5mm
U_CAN1, U_CAN2: MCP2515-xSO; SOIC-18W_7.5x11.6mm_P1.27mm
U_TRX1, U_TRX2: SN65HVD230; SOIC-8_3.9x4.9mm_P1.27mm
U_WDT1: MAX6369; SOT-23-8
Y1, Y2: 8MHz; Crystal_SMD_3225-4Pin_3.2x2.5mm

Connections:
+3V3: C2.1, C_CAN1_BULK1.1, C_CAN1_TRX1.1, C_CAN1_VDD1.1, C_CAN2_BULK2.1, C_CAN2_TRX2.1, C_CAN2_VDD2.1, R2.2, R3.1, R4.1, R_CAN1_RST1.2, R_CAN2_RST2.2, U1.36 (3V3), U4.8 (VCC), U_CAN1.18 (VDD), U_CAN2.18 (VDD), U_TRX1.3 (VCC), U_TRX2.3 (VCC), U_WDT1.8 (VCC)
+5V: C6.2, D_PWR1.1 (K), J2.8, U1.39 (VSYS)
/+5V_FROM_POWER: D_PWR1.2 (A), J1.1
CAN1_H: D1.1 (A1), J_CAN1_IN1.3, R_TERM_CAN1.2, U_TRX1.7 (CANH)
CAN1_L: D1.2 (A2), J_CAN1_IN1.2, SJ_TERM_CAN1.1 (A), U_TRX1.6 (CANL)
CAN2_H: D2.1 (A1), J_CAN2_IN2.3, R_TERM_CAN2.2, U_TRX2.7 (CANH)
CAN2_L: D2.2 (A2), J_CAN2_IN2.2, SJ_TERM_CAN2.1 (A), U_TRX2.6 (CANL)
CAN_RST_N: R_CAN1_RST1.1, R_CAN2_RST2.1, U1.10 (GPIO7), U_CAN1.17 (~RESET), U_CAN2.17 (~RESET)
CS_ENC1: J2.5, U1.22 (GPIO17)
CS_ENC2: J2.6, U1.26 (GPIO20)
CS_ENC3: J2.7, U1.27 (GPIO21)
ENC_MISO: J2.4, U1.21 (GPIO16)
ENC_MOSI: J2.3, U1.25 (GPIO19)
ENC_SCK: J2.2, U1.24 (GPIO18)
FAULT_N: J1.7, U1.9 (GPIO6)
GND: C2.2, C6.1, C_CAN1_BULK1.2, C_CAN1_OSC1.1, C_CAN1_OSC2.1, C_CAN1_TRX1.2, C_CAN1_VDD1.2, C_CAN2_BULK2.2, C_CAN2_OSC3.1, C_CAN2_OSC4.1, C_CAN2_TRX2.2, C_CAN2_VDD2.2, D1.3 (common), D2.3 (common), J1.2, J1.8, J1.SH, J2.1, J2.SH, J_CAN1_IN1.1, J_CAN2_IN2.1, R1.1, R5.2, R_CAN1_RS1.2, R_CAN2_RS2.2, U1.3 (GND), U1.8 (GND), U1.13 (GND), U1.18 (GND), U1.23 (GND), U1.28 (GND), U1.33 (GND), U1.38 (GND), U1.D2 (GND), U4.4 (GND), U4.5, U4.6, U_CAN1.9 (VSS), U_CAN2.9 (VSS), U_TRX1.2 (GND), U_TRX2.2 (GND), U_WDT1.2 (GND), Y1.2 (G), Y1.4 (G), Y2.2 (G), Y2.4 (G)
GP8: U1.11 (GPIO8), U_CAN2.16 (~CS)
GP9: U1.12 (GPIO9), U_CAN1.16 (~CS)
GP10: U1.14 (GPIO10), U_CAN1.13 (SCK), U_CAN2.13 (SCK)
GP11: U1.15 (GPIO11), U_CAN1.14 (SI), U_CAN2.14 (SI)
GP12: R_SO_SPI1.1, R_SO_SPI2.1, U1.16 (GPIO12)
GP13: U1.17 (GPIO13), U_CAN1.12 (~INT)
GP14: U1.19 (GPIO14), U_CAN2.12 (~INT)
GP15: U1.20 (GPIO15), U_WDT1.1 (WDI)
GP22: R1.2, U1.29 (GPIO22), U4.1
unnamed: R_TERM_CAN1.1, SJ_TERM_CAN1.2 (B)
unnamed: R_TERM_CAN2.1, SJ_TERM_CAN2.2 (B)
unnamed: C_CAN1_OSC2.2, U_CAN1.8 (OSC1), Y1.1
unnamed: C_CAN1_OSC1.2, U_CAN1.7 (OSC2), Y1.3
unnamed: R_SO_SPI1.2, U_CAN1.15 (SO)
unnamed: C_CAN2_OSC4.2, U_CAN2.8 (OSC1), Y2.1
unnamed: C_CAN2_OSC3.2, U_CAN2.7 (OSC2), Y2.3
unnamed: R_SO_SPI2.2, U_CAN2.15 (SO)
unnamed: R_CAN1_RS1.1, U_TRX1.8 (Rs)
unnamed: R_CAN2_RS2.1, U_TRX2.8 (Rs)
unnamed: R3.2, U_WDT1.4 (SET0)
unnamed: R4.2, U_WDT1.5 (SET1)
unnamed: R5.1, U_WDT1.6 (SET2)
unnamed: R2.1, U4.2, U_WDT1.7 (~WDO)
PWRGD_N: J1.6, U1.7 (GPIO5)
RXCAN1: U_CAN1.2 (RXCAN), U_TRX1.4 (R)
RXCAN2: U_CAN2.2 (RXCAN), U_TRX2.4 (R)
SAFETY_EN: J1.3, U4.7
TXCAN1: U_CAN1.1 (TXCAN), U_TRX1.1 (D)
TXCAN2: U_CAN2.1 (TXCAN), U_TRX2.1 (D)
VIN_RAW_MON: J1.4, U1.31 (GPIO26_ADC0)
VOUT_POST_FET_MON: J1.5, U1.32 (GPIO27_ADC1)
